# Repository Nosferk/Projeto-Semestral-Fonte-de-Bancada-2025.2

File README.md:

# Projeto-Semestral-Fonte-de-Bancada-2025.2

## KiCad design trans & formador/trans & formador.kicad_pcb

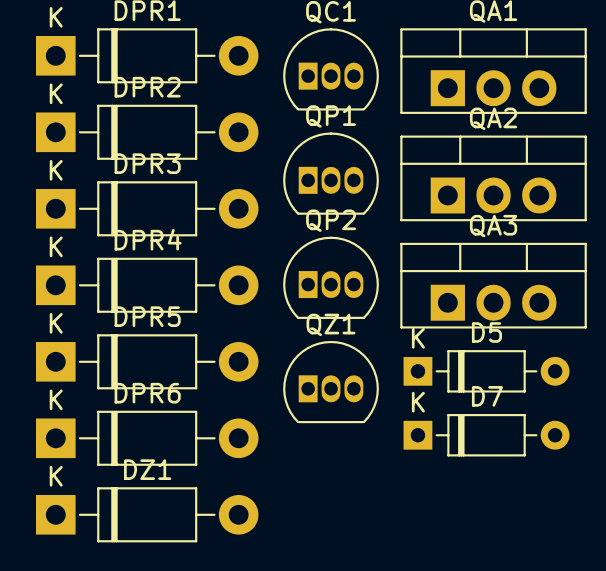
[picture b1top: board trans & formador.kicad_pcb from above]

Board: 2 copper layers, 16 parts (0 on the bottom side), 10 nets, no tracks yet.

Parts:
D5, D7: 1N4148; D_DO-35_SOD27_P7.62mm_Horizontal
DPR1, DPR2, DPR3, DPR4, DPR5, DPR6: 1N4002; D_DO-41_SOD81_P10.16mm_Horizontal
DZ1: 1N4752; D_DO-41_SOD81_P10.16mm_Horizontal
QA1, QA2, QA3: TIP122; TO-220-3_Vertical
QC1: BC547; TO-92_Inline
QP1: BC557; TO-92_Inline
QP2: BC547; TO-92_Inline
QZ1: BC547; TO-92_Inline

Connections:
unnamed: D5.2 (A), QZ1.2 (B)
unnamed: D5.1 (K), D7.1 (K), QP2.1 (C)
unnamed: D7.2 (A), QA1.1 (B), QA2.1 (B), QA3.1 (B)
unnamed: DPR1.2 (A), DPR2.1 (K)
unnamed: DPR1.1 (K), DPR4.1 (K), DPR6.1 (K), QP1.3 (E)
unnamed: DPR2.2 (A), DPR3.2 (A), DPR5.2 (A), DZ1.2 (A), QC1.3 (E), QP2.3 (E)
unnamed: DPR3.1 (K), DPR4.2 (A)
unnamed: DPR5.1 (K), DPR6.2 (A)
unnamed: DZ1.1 (K), QZ1.1 (C)
unnamed: QA1.2 (C), QA2.2 (C), QA3.2 (C)
